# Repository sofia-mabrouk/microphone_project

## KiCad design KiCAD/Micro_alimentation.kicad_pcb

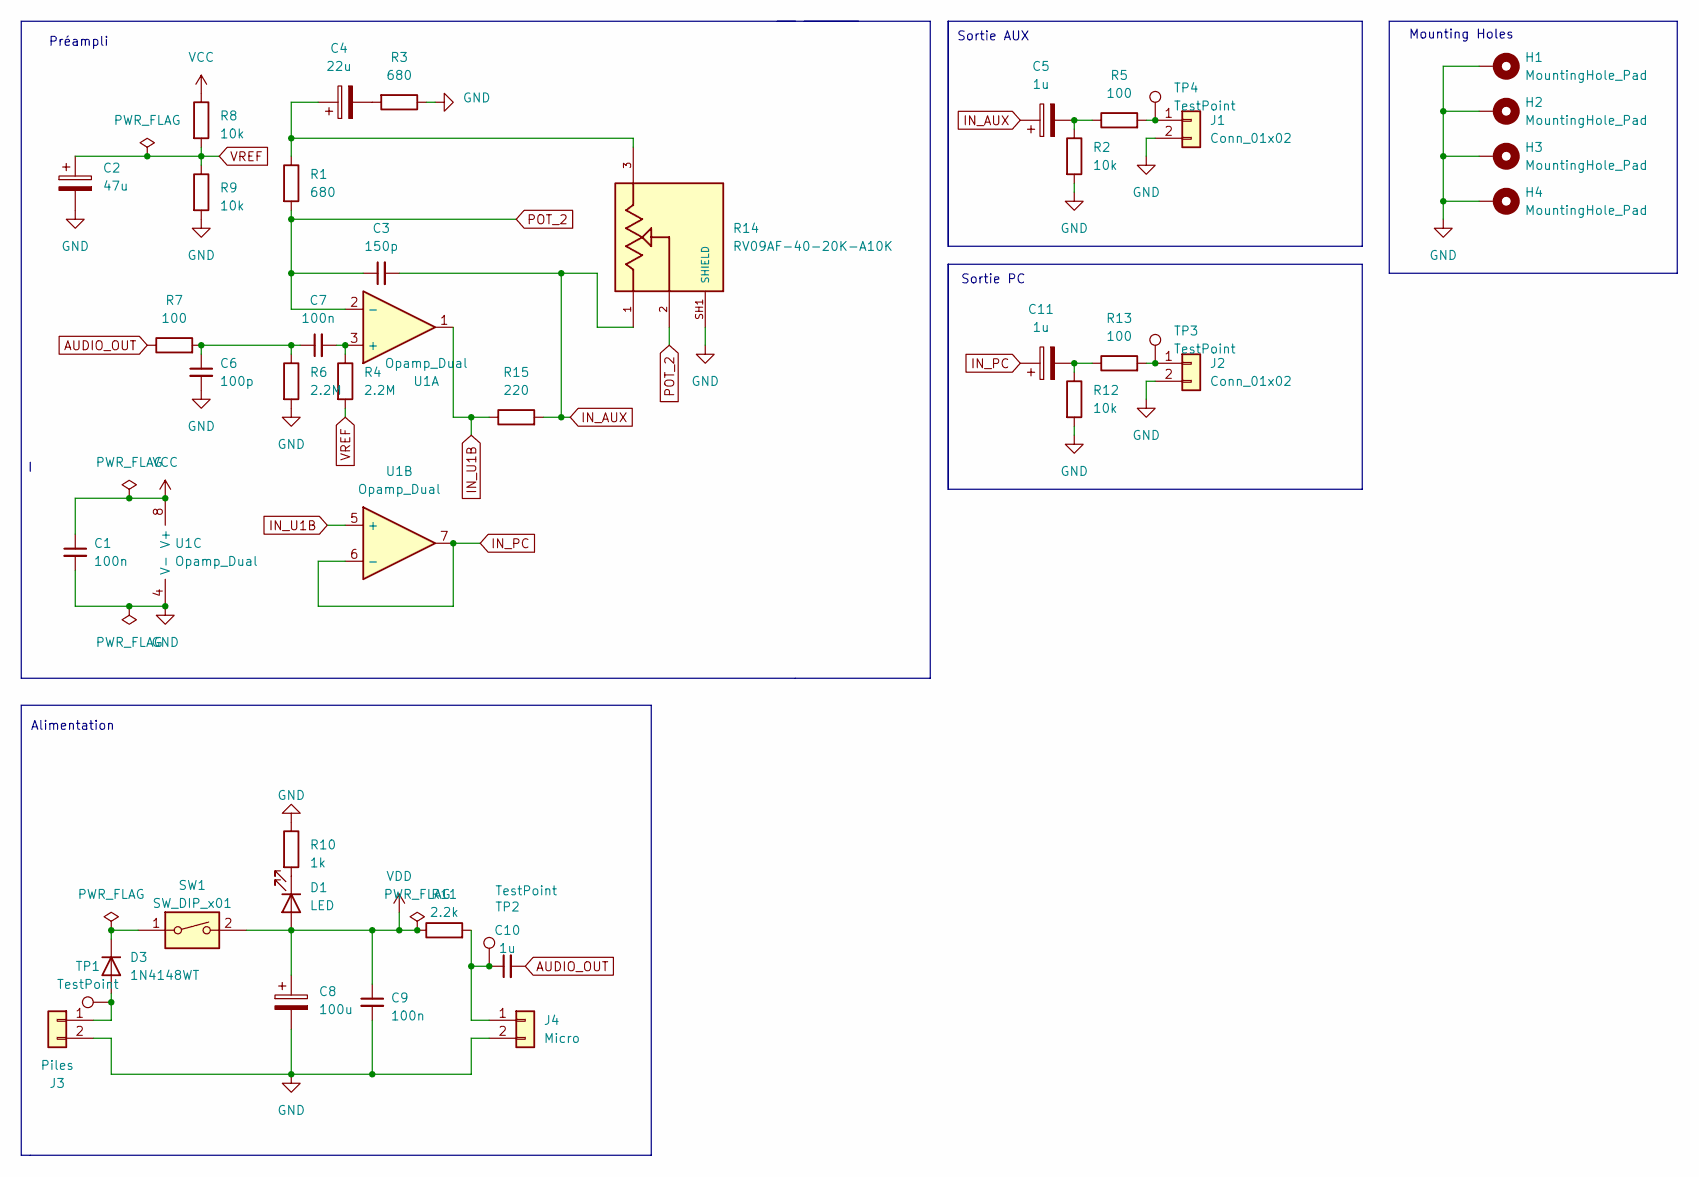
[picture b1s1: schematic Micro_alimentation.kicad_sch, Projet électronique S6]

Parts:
C1, C7, C9: 100n; C_0805_2012Metric_Pad1.18x1.45mm_HandSolder
C2: 47u; CP_Elec_6.3x5.7
C3: 150p; C_0805_2012Metric_Pad1.18x1.45mm_HandSolder
C4: 22u; C_0805_2012Metric_Pad1.18x1.45mm_HandSolder
C5, C10, C11: 1u; C_0805_2012Metric_Pad1.18x1.45mm_HandSolder
C6: 100p; C_0805_2012Metric_Pad1.18x1.45mm_HandSolder
C8: 100u; CP_Elec_6.3x5.7
D1: LED; LED_1206_3216Metric_Pad1.42x1.75mm_HandSolder
D3: 1N4148WT; D_0805_2012Metric_Pad1.15x1.40mm_HandSolder
H1, H2, H3, H4: MountingHole_Pad; MountingHole_3.2mm_M3_DIN965_Pad
J1, J2: Conn_01x02; JST_PH_S2B-PH-K_1x02_P2.00mm_Horizontal
J3: Piles; JST_PH_S2B-PH-K_1x02_P2.00mm_Horizontal
J4: Micro; JST_PH_S2B-PH-K_1x02_P2.00mm_Horizontal
R1, R3: 680; R_0805_2012Metric_Pad1.20x1.40mm_HandSolder
R2, R8, R9, R12: 10k; R_0805_2012Metric_Pad1.20x1.40mm_HandSolder
R4, R6: 2.2M; R_0805_2012Metric_Pad1.20x1.40mm_HandSolder
R5, R7, R13: 100; R_0805_2012Metric_Pad1.20x1.40mm_HandSolder
R10: 1k; R_0805_2012Metric_Pad1.20x1.40mm_HandSolder
R11: 2.2k; R_0805_2012Metric_Pad1.20x1.40mm_HandSolder
R14: RV09AF-40-20K-A10K; TRIM_RV09AF-40-20K-A10K; PARTREV N/A
R15: 220; R_0805_2012Metric_Pad1.20x1.40mm_HandSolder
SW1: SW_DIP_x01; SW_Slide-03_Wuerth-WS-SLTV_10x2.5x6.4_P2.54mm
TP1, TP2, TP3, TP4: TestPoint; TestPoint_Bridge_Pitch2.0mm_Drill0.7mm
U1: Opamp_Dual; SOIC-8_3.9x4.9mm_P1.27mm

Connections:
AUDIO_OUT: C10.2, R7.1
GND: C1.2, C2.2, C6.2, C8.2, C9.2, H1.1, H2.1, H3.1, H4.1, J1.2, J2.2, J3.2, J4.2, R2.2, R3.1, R6.2, R9.2, R10.1, R12.2, R14.SH1 (SHIELD), R14.SH2 (SHIELD), U1.4 (V-)
IN_AUX: C3.2, C5.1, R14.1, R15.2
IN_PC: C11.1, U1.6 (-), U1.7
IN_U1B: R15.1, U1.1, U1.5 (+)
unnamed: C4.1, R1.1, R14.3
unnamed: C4.2, R3.2
unnamed: C5.2, R2.1, R5.1
unnamed: C6.1, C7.1, R6.1, R7.2
unnamed: C11.2, R12.1, R13.1
unnamed: D1.1 (K), R10.2
unnamed: D3.2 (A), J3.1, TP1.1
unnamed: D3.1 (K), SW1.1
unnamed: J1.1, R5.2, TP4.1
unnamed: J2.1, R13.2, TP3.1
unnamed: C10.1, J4.1, R11.2, TP2.1
unnamed: C7.2, R4.1, U1.3 (+)
POT_2: C3.1, R1.2, R14.2, U1.2 (-)
VCC: C1.1, R8.1, U1.8 (V+)
VDD: C8.1, C9.1, D1.2 (A), R11.1, SW1.2
VREF: C2.1, R4.2, R8.2, R9.1

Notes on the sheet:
Préampli
Sortie PC
Alimentation
Sortie AUX
Mounting Holes

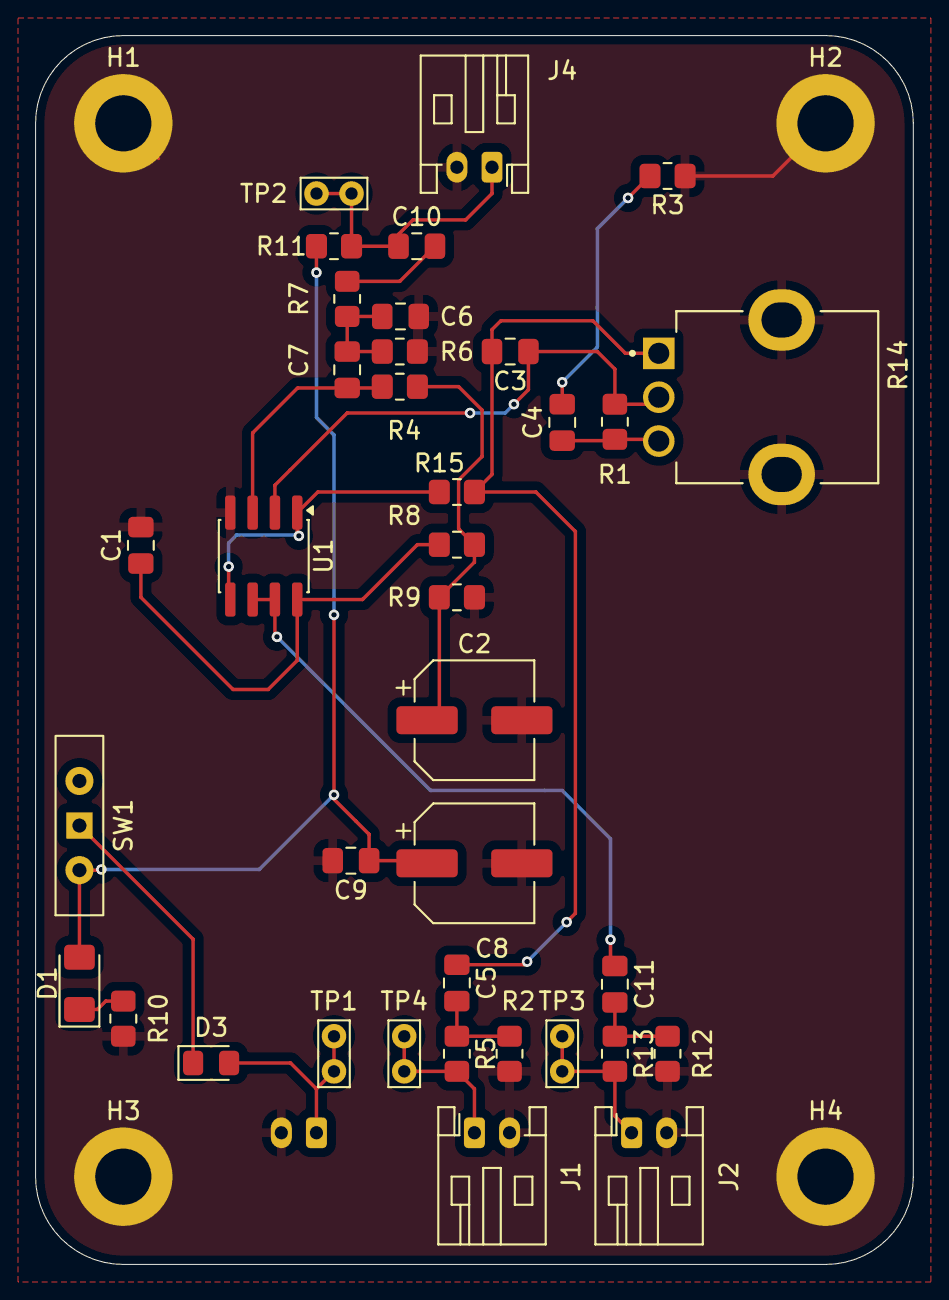
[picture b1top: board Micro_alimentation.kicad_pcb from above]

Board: 4 copper layers, 50.0 x 70.0 mm, 42 parts (1 on the bottom side), 21 nets.

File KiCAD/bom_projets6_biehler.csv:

"Reference","Qty","Value","DNP","Exclude from BOM","Exclude from Board","Footprint","Datasheet"
"C1,C7,C9","3","100n","","","","Capacitor_SMD:C_0805_2012Metric_Pad1.18x1.45mm_HandSolder","~"
"C2","1","47u","","","","Capacitor_SMD:CP_Elec_6.3x5.7","~"
"C3","1","150p","","","","Capacitor_SMD:C_0805_2012Metric_Pad1.18x1.45mm_HandSolder","~"
"C4","1","22u","","","","Capacitor_SMD:C_0805_2012Metric_Pad1.18x1.45mm_HandSolder","~"
"C5,C10,C11","3","1u","","","","Capacitor_SMD:C_0805_2012Metric_Pad1.18x1.45mm_HandSolder","~"
"C6","1","100p","","","","Capacitor_SMD:C_0805_2012Metric_Pad1.18x1.45mm_HandSolder","~"
"C8","1","100u","","","","Capacitor_SMD:CP_Elec_6.3x5.7","~"
"D1","1","LED","","","","LED_SMD:LED_1206_3216Metric_Pad1.42x1.75mm_HandSolder","~"
"D3","1","1N4148WT","","","","Diode_SMD:D_0805_2012Metric_Pad1.15x1.40mm_HandSolder","https://www.diodes.com/assets/Datasheets/ds30396.pdf"
"H1,H2,H3,H4","4","MountingHole_Pad","","Excluded from BOM","","MountingHole:MountingHole_3.2mm_M3_DIN965_Pad","~"
"J1,J2","2","Conn_01x02","","","","Connector_JST:JST_PH_S2B-PH-K_1x02_P2.00mm_Horizontal","~"
"J3","1","Piles","","","","Connector_JST:JST_PH_S2B-PH-K_1x02_P2.00mm_Horizontal","~"
"J4","1","Micro","","","","Connector_JST:JST_PH_S2B-PH-K_1x02_P2.00mm_Horizontal","~"
"R1,R3","2","680","","","","Resistor_SMD:R_0805_2012Metric_Pad1.20x1.40mm_HandSolder","~"
"R2,R8,R9,R12","4","10k","","","","Resistor_SMD:R_0805_2012Metric_Pad1.20x1.40mm_HandSolder","~"
"R4,R6","2","2.2M","","","","Resistor_SMD:R_0805_2012Metric_Pad1.20x1.40mm_HandSolder","~"
"R5,R7,R13","3","100","","","","Resistor_SMD:R_0805_2012Metric_Pad1.20x1.40mm_HandSolder","~"
"R10","1","1k","","","","Resistor_SMD:R_0805_2012Metric_Pad1.20x1.40mm_HandSolder","~"
"R11","1","2.2k","","","","Resistor_SMD:R_0805_2012Metric_Pad1.20x1.40mm_HandSolder","~"
"R14","1","RV09AF-40-20K-A10K","","","","RV09AF-40-20K-A10K:TRIM_RV09AF-40-20K-A10K",""
"R15","1","220","","","","Resistor_SMD:R_0805_2012Metric_Pad1.20x1.40mm_HandSolder","~"
"SW1","1","SW_DIP_x01","","","","Button_Switch_THT:SW_Slide-03_Wuerth-WS-SLTV_10x2.5x6.4_P2.54mm","~"
"TP1,TP2,TP3,TP4","4","TestPoint","","","","TestPoint:TestPoint_Bridge_Pitch2.0mm_Drill0.7mm","~"
"U1","1","Opamp_Dual","","","","Package_SO:SOIC-8_3.9x4.9mm_P1.27mm","~"

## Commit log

2026-03-09 Setup du projet: fichiers KiCAD, sources, datasheets
2026-03-12 Update : PCB + bom
2026-03-12 Added .gitignore and README.md files
2026-03-12 Modified .gitignore to ignore backup files
